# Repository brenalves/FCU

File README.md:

# Gravitum Flight Control Unit

Author: Breno Soares Alves

That project aims to assembly from scratch a flight control unit capable of GNSS-waypoint navigation to my undergraduate work in Computer Science in Federal University of Fronteira Sul. The Gravitum FCU encapsulates basic components to achieve great reliability and precision with embedded sensors, supply management, channels for output servos and extra modules.

That repository maintain each process to reach the final result. The project structure is organized as follow:

- /airplane: Project for self-made single engine, electric fixed wing aircraft. Here you may find 3D Models, annotations and schematics;
- /doc: Monography of the project, documental final result for the entire project;
- /pcb: Project for the Printed Circuit Board (Hardware). Here you may find electrical information, schematics, annotations and the board itself. Software: KICAD;
- /src: Project for the library and drivers (Software) that will control the airplane using the hardware. Here you will find the source code of each driver for sensors, PWM, comms protocols and etc. Software: STM32CUBEIDE.

## Objectives and Proof of Concept

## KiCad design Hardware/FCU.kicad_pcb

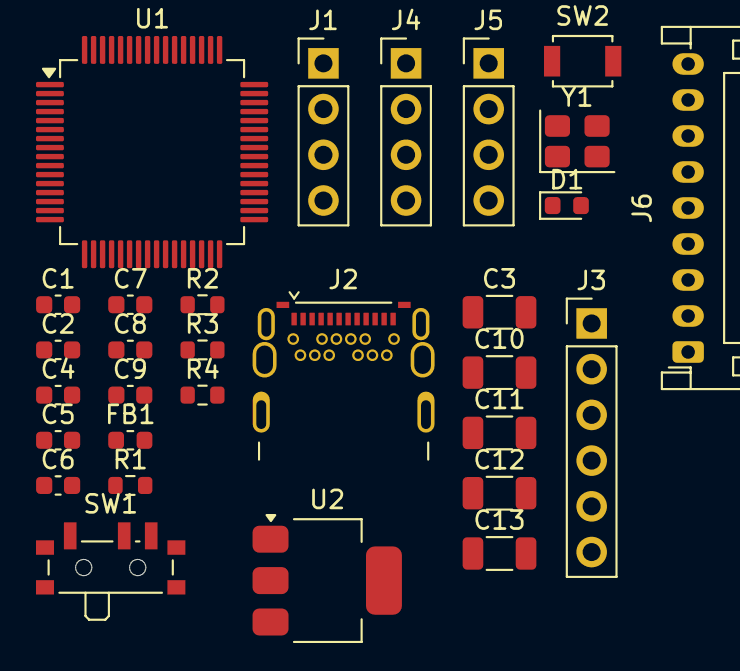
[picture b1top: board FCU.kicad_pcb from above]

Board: 2 copper layers, 30 parts (0 on the bottom side), 31 nets, no tracks yet.

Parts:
C1, C2: 30p; C_0603_1608Metric
C3: 10u; C_1206_3216Metric
C4, C5, C6, C7, C8: 100n; C_0603_1608Metric
C9: 10n; C_0603_1608Metric
C10, C12: 1u; C_1206_3216Metric
C11, C13: 22u; C_1206_3216Metric
D1: LED; LED_0603_1608Metric
FB1: 120R; L_0603_1608Metric
J1, J4, J5: Conn_01x04_Pin; PinHeader_1x04_P2.54mm_Vertical
J2: USB_C_Receptacle_USB2.0_16P; USB_C_Receptacle_CNCTech_C-ARA1-AK51X
J3: Conn_01x06_Pin; PinHeader_1x06_P2.54mm_Vertical
J6: Conn_01x09_Pin; JST_PH_S9B-PH-K_1x09_P2.00mm_Horizontal
R1, R2: 5k1; R_0603_1608Metric
R3: 10k; R_0603_1608Metric
R4: 1k5; R_0603_1608Metric
SW1: SW_SPDT; SW_SPDT_PCM12
SW2: SW_Push; SW_SPST_B3U-1000P
U1: STM32F405RGTx; LQFP-64_10x10mm_P0.5mm
U2: AMS1117-3.3; SOT-223-3_TabPin2
Y1: 8MHz; Crystal_SMD_3225-4Pin_3.2x2.5mm

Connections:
+3.3V: C3.1, C4.1, C5.1, C6.1, C7.1, C8.1, C12.1, C13.1, D1.2 (A), FB1.2, J1.1, J3.1, J4.1, J5.1, J6.1, SW1.3 (C), U1.1 (VBAT), U1.19 (VDD), U1.32 (VDD), U1.48 (VDD), U1.64 (VDD), U2.2 (VO)
+3.3VA: C9.1, C10.1, FB1.1, U1.13 (VDDA)
/SW_BOOT0: R3.1, SW1.2 (B)
BOOT0: R3.2, U1.60 (BOOT0)
GND: C1.2, C2.2, C3.2, C4.2, C5.2, C6.2, C7.2, C8.2, C9.2, C10.2, C11.2, C12.2, C13.2, J1.4, J2.A1 (GND), J2.A12 (GND), J2.B1 (GND), J2.B12 (GND), J3.6, J4.4, J5.4, J6.9, R1.1, R2.1, R4.2, SW1.1 (A), SW2.1, U1.12 (VSSA), U1.18 (VSS), U1.63 (VSS), U2.1 (GND), Y1.2, Y1.4
I2C1_SCL: J5.3, U1.58 (PB6)
I2C1_SDA: J5.2, U1.59 (PB7)
NRST: SW2.2, U1.7 (NRST)
unnamed: D1.1 (K), R4.1
unnamed: J2.A5 (CC1), R2.2
unnamed: J2.B5 (CC2), R1.2
RCC_OSC_IN: C1.1, U1.5 (PH0), Y1.1
RCC_OSC_OUT: C2.1, U1.6 (PH1), Y1.3
SDIO_CK: J6.2, U1.53 (PC12)
SDIO_CMD: J6.3, U1.54 (PD2)
SDIO_D0: J6.4, U1.39 (PC8)
SDIO_D1: J6.5, U1.40 (PC9)
SDIO_D2: J6.6, U1.51 (PC10)
SDIO_D3: J6.7, U1.52 (PC11)
SD_STS: J6.8, U1.50 (PA15)
SPI1_MISO: J3.3, U1.22 (PA6)
SPI1_MOSI: J3.4, U1.23 (PA7)
SPI1_NCS: J3.5, U1.26 (PB0)
SPI1_SCK: J3.2, U1.21 (PA5)
SYS_SWCLK: J1.2, U1.49 (PA14)
SYS_SWDIO: J1.3, U1.46 (PA13)
USART1_RX: J4.3, U1.43 (PA10)
USART1_TX: J4.2, U1.42 (PA9)
USB_D+: J2.A6 (D+), J2.B6 (D+), U1.45 (PA12)
USB_D-: J2.A7 (D-), J2.B7 (D-), U1.44 (PA11)
VBUS: C11.1, J2.A4 (VBUS), J2.A9 (VBUS), J2.B4 (VBUS), J2.B9 (VBUS), U2.3 (VI)

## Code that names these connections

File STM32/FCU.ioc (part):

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Mcu.Name=STM32F405RGTx
Mcu.Package=LQFP64
Mcu.UserName=STM32F405RGTx
PA10.Mode=Asynchronous
PA10.Signal=USART1_RX
PA11.Mode=Device_Only
PA11.Signal=USB_OTG_FS_DM
PA12.Mode=Device_Only
PA12.Signal=USB_OTG_FS_DP
PA13.Mode=Serial_Wire
PA13.Signal=SYS_JTMS-SWDIO
PA14.Mode=Serial_Wire
PA14.Signal=SYS_JTCK-SWCLK
PA15.GPIOParameters=GPIO_Label
PA15.GPIO_Label=SD_STS
PA15.Signal=GPIO_Input
PA5.Mode=Full_Duplex_Master
PA5.Signal=SPI1_SCK
PA6.Mode=Full_Duplex_Master
PA6.Signal=SPI1_MISO
PA7.Mode=Full_Duplex_Master
PA7.Signal=SPI1_MOSI
PA9.Mode=Asynchronous
PA9.Signal=USART1_TX
PB6.Mode=I2C
PB6.Signal=I2C1_SCL
PB7.Mode=I2C
PB7.Signal=I2C1_SDA
PC10.Mode=SD_4_bits_Wide_bus
PC10.Signal=SDIO_D2
PC11.Mode=SD_4_bits_Wide_bus
PC11.Signal=SDIO_D3
PC12.Mode=SD_4_bits_Wide_bus
PC12.Signal=SDIO_CK
PC4.GPIOParameters=GPIO_Label
PC4.GPIO_Label=SPI1_NCS
PC4.Signal=GPIO_Output
PC8.Mode=SD_4_bits_Wide_bus
PC8.Signal=SDIO_D0
PC9.Mode=SD_4_bits_Wide_bus
PC9.Signal=SDIO_D1
PD2.Mode=SD_4_bits_Wide_bus
PD2.Signal=SDIO_CMD
PH0-OSC_IN.Mode=HSE-External-Oscillator
PH0-OSC_IN.Signal=RCC_OSC_IN
PH1-OSC_OUT.Mode=HSE-External-Oscillator
PH1-OSC_OUT.Signal=RCC_OSC_OUT
RCC.HSE_VALUE=8000000
RCC.SYSCLKFreq_VALUE=168000000
RCC.SYSCLKSource=RCC_SYSCLKSOURCE_PLLCLK
board=custom

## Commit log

2025-09-10 first commit (just a simple serial protocols test circuit)
2025-09-11 created FCU symbol and footprint libraries, add documentation, did some tests in STM32 project
2025-09-12 added some readme notes
2025-09-15 name changed to hardware, power supply schematic done but need review
2025-09-15 added pdf schematic
2025-10-31 doc: continuing chapter 2
2025-10-31 doc: flight dynamics theoretical framework
2025-11-01 doc: flight dynamics done
2025-11-07 simulation with jsbsim
2025-11-07 simulation with graph plot
2025-11-09 changed logic to get and set data
2025-11-10 simulation: interface changed getvalue and setvalue to string
2025-11-11 simulation: starting pid control
2025-11-12 doc: fixed professor comments chapter 2 and 3
